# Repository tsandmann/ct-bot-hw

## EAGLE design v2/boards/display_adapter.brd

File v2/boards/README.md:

# ct-Bot v2 prototype boards

These boards (mainboard, teensy mcu board, and sensor boards) are ***prototypes*** just for ***development and testing***. They are provided "as is" without warranty of any kind.

## Known issues and notes

Please note: these problem lists may be highly incomplete, as not all functions have been tested yet!

### [Mainboard](../schematics/mainboard_0.9.2.pdf)

* Positioning of J2 is inappropriate
* TBC

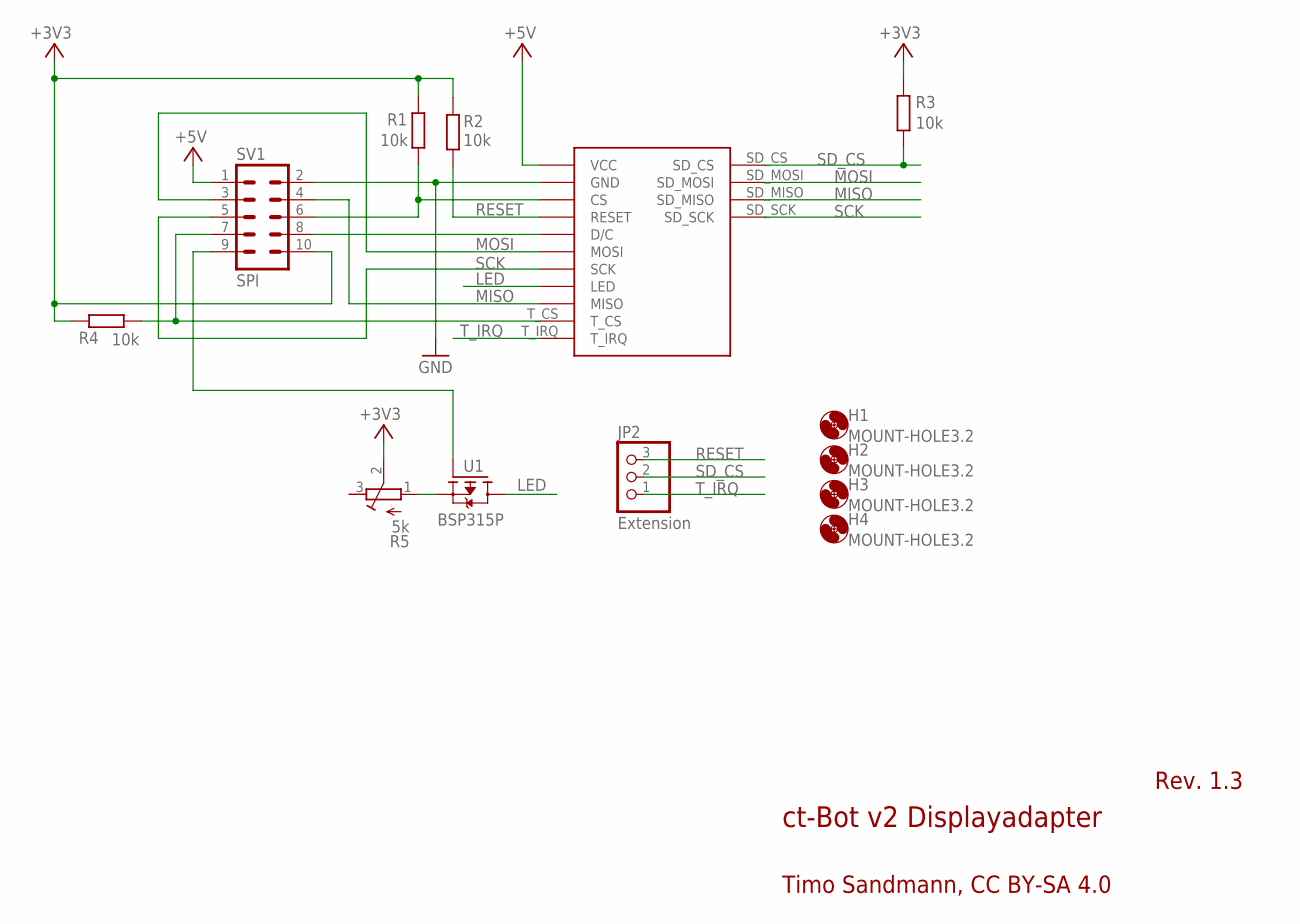
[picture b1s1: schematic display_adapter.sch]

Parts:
H1, H2, H3, H4: MOUNT-HOLE3.2; 3,2
J1: SPI_TFT_DISPLAY_TOUCH; SPI_DISPLAY_TOUCH
JP2: Extension; 1X03
R1, R2, R3, R4: 10k; 0204/7
R5: 5k; RTRIM64W
SV1: SPI; ML10
U1: BSP315P; PG-SOT-223

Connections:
+3V3: R1.2, R2.2, R3.2, R4.2, R5.2 (S), SV1.10
+5V: J1.VCC, SV1.1
GND: J1.GND, SV1.2
LED: J1.LED, U1.2 (D), U1.4 (D)
MISO: J1.MISO, J1.SD_MISO, J1.T_MISO (MISO), SV1.4
MOSI: J1.MOSI, J1.SD_MOSI, J1.T_MOSI (MOSI), SV1.3
unnamed: SV1.9, U1.1 (G)
unnamed: R5.1 (A), U1.3 (S)
unnamed: J1.CS, R1.1, SV1.6
unnamed: J1.D/C, SV1.8
unnamed: J1.T_CS, R4.1, SV1.7
RESET: J1.RESET, JP2.3, R2.1
SCK: J1.SCK, J1.SD_SCK, J1.T_SCK (SCK), SV1.5
SD_CS: J1.SD_CS, JP2.2, R3.1
T_IRQ: J1.T_IRQ, JP2.1

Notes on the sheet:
ct-Bot v2 Displayadapter
Rev. 1.3
Timo Sandmann, CC BY-SA 4.0

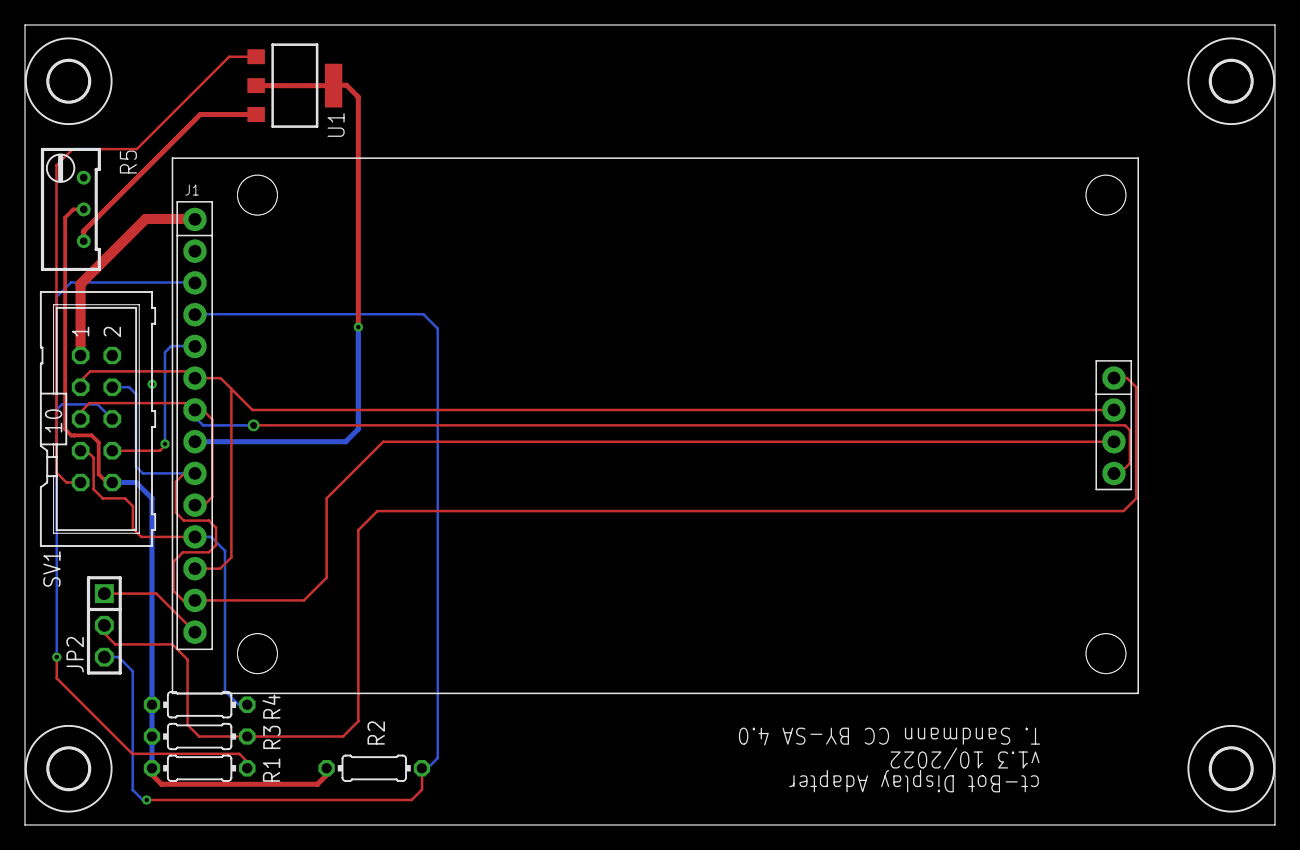
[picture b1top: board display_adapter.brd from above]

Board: 2 copper layers, 100.0 x 64.0 mm, 13 parts (0 on the bottom side), 15 nets.

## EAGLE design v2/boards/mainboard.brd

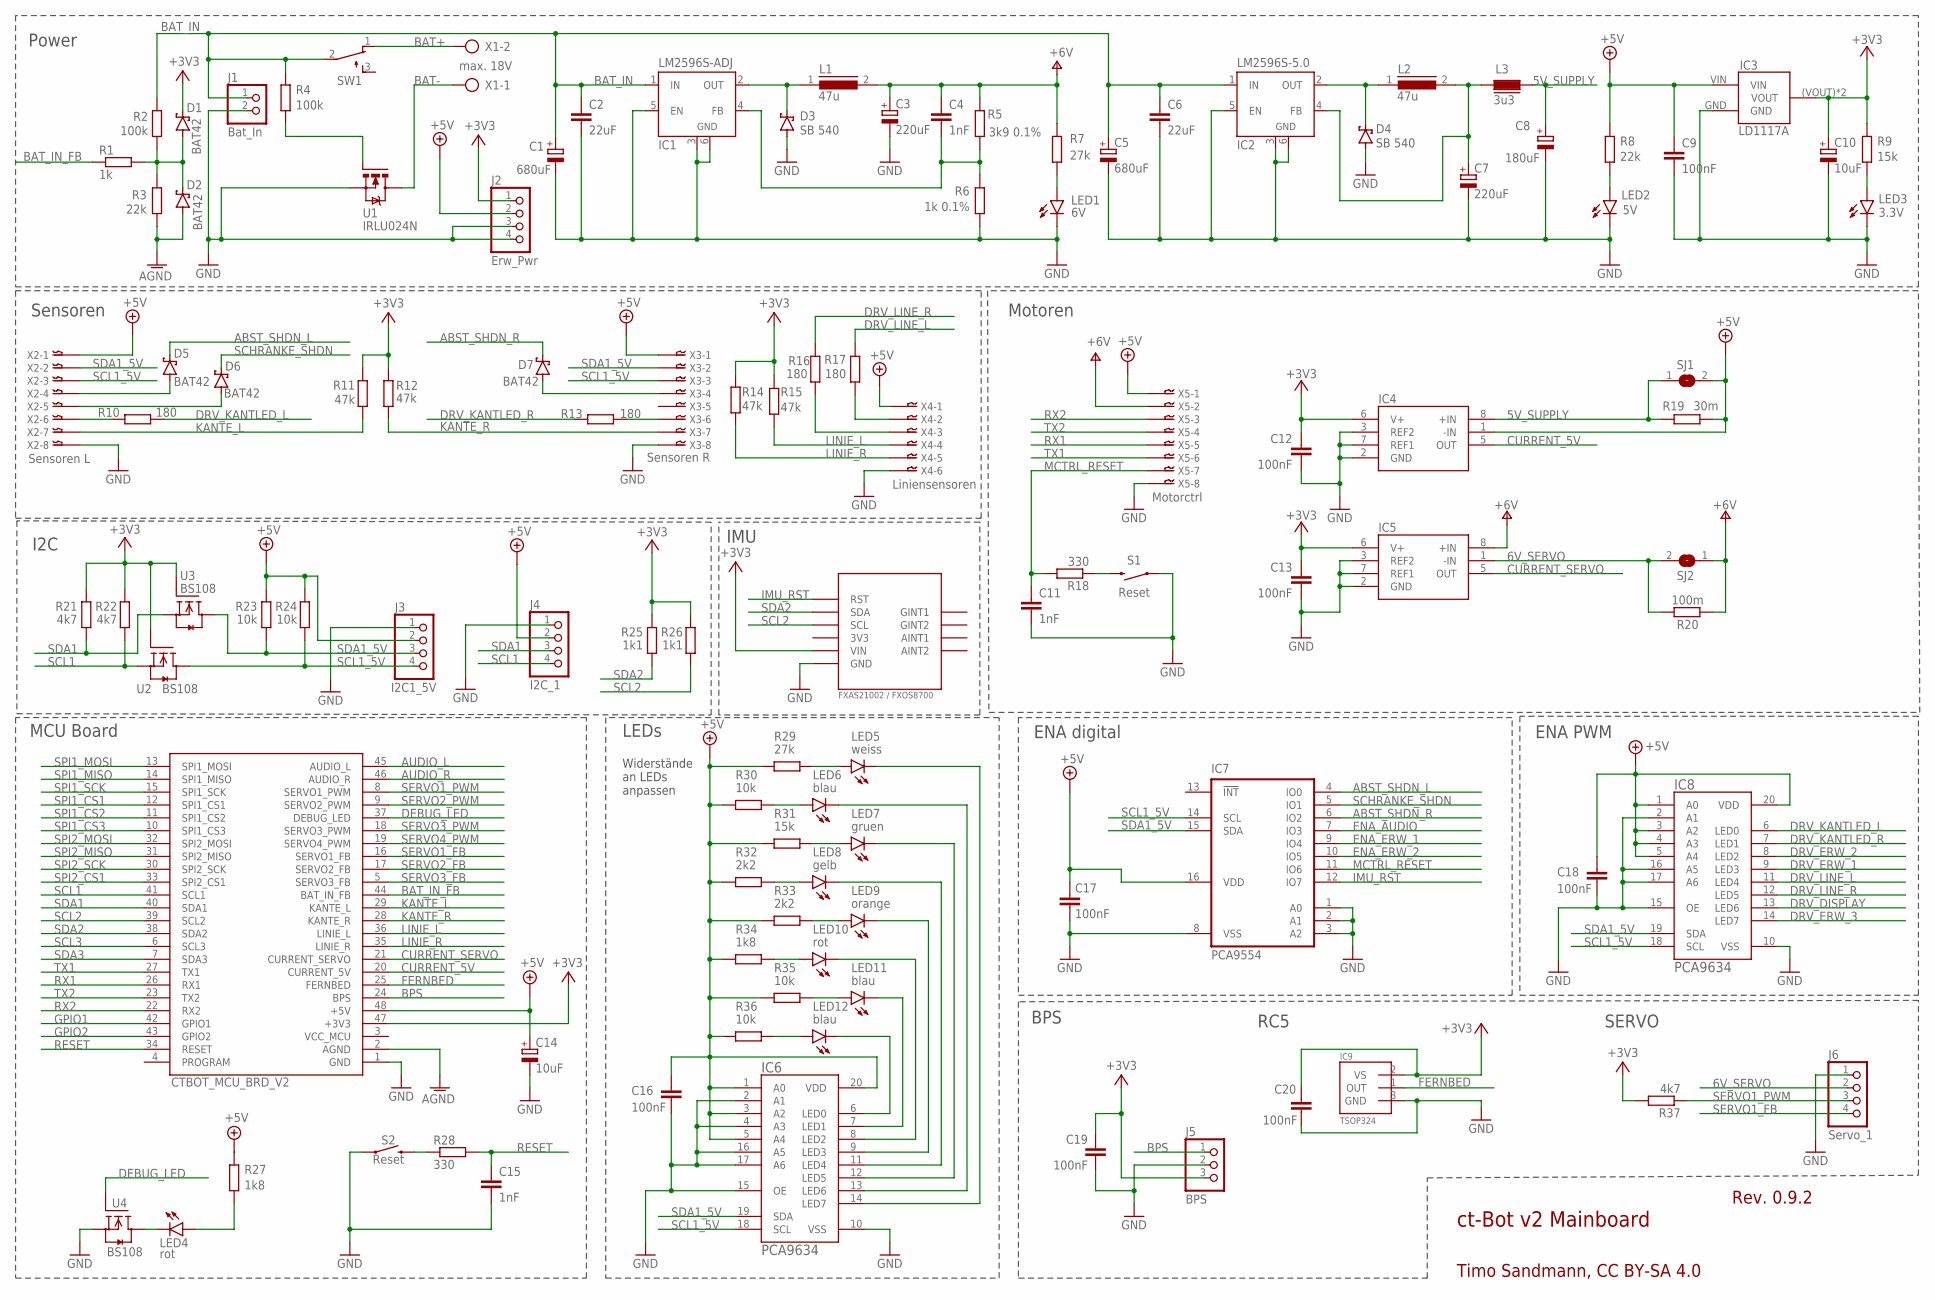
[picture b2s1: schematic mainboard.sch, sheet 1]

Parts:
C1, C5: 680uF; E5-10,5
C2, C6: 22uF; C025-025X050
C3, C7: 220uF; E5-10,5
C4, C11, C15: 1nF; C025-025X050
C8: 180uF; E3,5-8
C9, C16, C17, C18, C19, C20: 100nF; C025-025X050
C10: 10uF; E2-5
C12, C13: 100nF; C0805
C14: 10uF; TT2D5L
D1, D2: BAT42; DO35-7
D3, D4: SB 540; DO201T15
D5, D6, D7: BAT42; 0207/2V
IC1: LM2596S-ADJ; TO263-5
IC2: LM2596S-5.0; TO263-5
IC3: LD1117A; LD1117SOT-223
IC4, IC5: INA28AID; SO08
IC6, IC8: PCA9634; SO20W
IC7: PCA9554; SO16W
IC9: TSOP324
J1: Bat_In; 1X02
J2: Erw_Pwr; 1X04
J3: I2C1_5V; 1X04
J4: I2C_1; 1X04
J5: BPS; 1X03
J6: Servo_1; 1X04
L1, L2: 47u; 09HCP
L3: 3u3; FASTRON_07HCP_INDUCTOR
LED1: 6V; LED3MM
LED2: 5V; LED3MM
LED3: 3.3V; LED3MM
LED4, LED10: rot; LED3MM
LED5: weiss; LED3MM
LED6, LED11, LED12: blau; LED3MM
LED7: gruen; LED3MM
LED8: gelb; LED3MM
LED9: orange; LED3MM
MCU: CTBOT_MCU_BRD_V2; DIP48
R1: 1k; 0204/7
R2: 100k; 0204/7
R3: 22k; 0204/7
R4: 100k; 0204V
R5: 3k9 0.1%; 0204V
R6: 1k 0.1%; 0204V
R7, R29: 27k; 0204V
R8: 22k; 0204V
R9, R31: 15k; 0204V
R10, R13, R16, R17: 180; 0204V
R11, R12: 47k; 0204V
R14, R15: 47k; 0204/7
R18, R28: 330; 0204V
R19: 30m; R2512
R20: 100m; R2512
R21, R22, R37: 4k7; 0204/7
R23, R24, R30, R35, R36: 10k; 0204V
R25, R26: 1k1; 0204/7
R27, R34: 1k8; 0204V
R32, R33: 2k2; 0204V
S1, S2: Reset; TACTILE_SWITCH_PTH_6.0MM
SJ1, SJ2: SJ
SW1: TL32PO; TL3XPO
U1: IRLU024N; TO251AA
U2, U3, U4: BS108; SOT54E
U$10: IMU; NXP_9DOF
X1: max. 18V; AK500/2-H
X2: Sensoren L; B8B-XH
X3: Sensoren R; B8B-XH
X4: Liniensensoren; B6B-XH
X5: Motorctrl; B8B-XH

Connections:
5V_SUPPLY: C8.+, IC4.8 (+IN), L3.2, R19.1, SJ1.1
6V_SERVO: IC5.1 (-IN), J6.2, R20.2, SJ2.2; also elsewhere on the board
+3V3: C10.+, C12.1, C13.1, C19.1, C20.1, D1.C, IC3.(VOUT) (VOUT), IC3.VOUT, IC4.6 (V+), IC5.6 (V+), IC9.2 (VS), J2.1, J5.3, MCU.47 (+3V3), R9.2, R11.2, R12.1, R14.2, R15.2, R21.2, R22.2, R25.2, R26.2, R37.2, U2.G, U3.G, U$10.VIN; also elsewhere on the board
+5V: C9.1, C14.+, C16.1, C17.1, C18.1, IC3.VIN, IC4.1 (-IN), IC6.1 (A0), IC6.3 (A2), IC6.5 (A4), IC6.20 (VDD), IC7.16 (VDD), IC8.1 (A0), IC8.3 (A2), IC8.4 (A3), IC8.5 (A4), IC8.20 (VDD), J2.2, J3.2, J4.2, MCU.48 (+5V), R8.2, R19.2, R23.2, R24.2, R27.2, R29.1, R30.1, R31.1, R32.1, R33.1, R34.1, R35.1, R36.1, SJ1.2, X2.P$1, X3.P$1, X4.P$1, X5.P$1; also elsewhere on the board
+6V: C3.+, C4.1, IC5.8 (+IN), L1.2, R5.2, R7.1, R20.1, SJ2.1, X5.P$2
ABST_SHDN_L: D5.2 (C), IC7.4 (IO0)
ABST_SHDN_R: D7.2 (C), IC7.6 (IO2)
AGND: D2.A, MCU.2 (AGND), R3.1; also elsewhere on the board
AUDIO_L: MCU.45 (AUDIO_L); also elsewhere on the board
AUDIO_R: MCU.46 (AUDIO_R); also elsewhere on the board
BAT+: SW1.1 (O), X1.2
BAT-: U1.2 (D), U1.4 (D), X1.1
BAT_IN: C1.+, C2.1, C5.+, C6.1, IC1.1 (IN), IC2.1 (IN), J1.1, R2.2, R4.2, SW1.2; also elsewhere on the board
BAT_IN_FB: MCU.44 (BAT_IN_FB), R1.1
BPS: J5.1, MCU.24 (BPS)
CURRENT_5V: IC4.5 (OUT), MCU.20 (CURRENT_5V)
CURRENT_SERVO: IC5.5 (OUT), MCU.21 (CURRENT_SERVO)
DEBUG_LED: MCU.37 (DEBUG_LED), U4.G
DRV_DISPLAY: IC8.13 (LED6); also elsewhere on the board
DRV_ERW_1: IC8.9 (LED3); also elsewhere on the board
DRV_ERW_2: IC8.8 (LED2); also elsewhere on the board
DRV_ERW_3: IC8.14 (LED7); also elsewhere on the board
DRV_KANTLED_L: IC8.6 (LED0), R10.2
DRV_KANTLED_R: IC8.7 (LED1), R13.1
DRV_LINE_L: IC8.11 (LED4), R17.2
DRV_LINE_R: IC8.12 (LED5), R16.2
ENA_AUDIO: IC7.7 (IO3); also elsewhere on the board
ENA_ERW_1: IC7.9 (IO4); also elsewhere on the board
ENA_ERW_2: IC7.10 (IO5); also elsewhere on the board
FERNBED: IC9.1 (OUT), MCU.25 (FERNBED)
GND: C1.-, C2.2, C3.-, C5.-, C6.2, C7.-, C8.-, C9.2, C10.-, C11.2, C12.2, C13.2, C14.-, C15.2, C16.2, C17.2, C18.2, C19.2, C20.2, D3.A, D4.A, IC1.3 (GND), IC1.5 (EN), IC1.6 (GND), IC2.3 (GND), IC2.5 (EN), IC2.6 (GND), IC3.GND, IC4.2 (GND), IC4.3 (REF2), IC4.7 (REF1), IC5.2 (GND), IC5.3 (REF2), IC5.7 (REF1), IC6.2 (A1), IC6.4 (A3), IC6.10 (VSS), IC6.15 (OE), IC6.16 (A5), IC6.17 (A6), IC7.1 (A0), IC7.2 (A1), IC7.3 (A2), IC7.8 (VSS), IC8.2 (A1), IC8.10 (VSS), IC8.15 (OE), IC8.16 (A5), IC8.17 (A6), IC9.3 (GND), J1.2, J2.3, J2.4, J3.1, J4.1, J5.2, J6.1, LED1.K (C), LED2.K (C), LED3.K (C), MCU.1 (GND), R6.1, S1.1, S2.1, U1.3 (S), U4.S, U$10.GND, X2.P$8, X3.P$8, X4.P$6, X5.P$8; also elsewhere on the board
GPIO1: MCU.42 (GPIO1); also elsewhere on the board
GPIO2: MCU.43 (GPIO2); also elsewhere on the board
IMU_RST: IC7.12 (IO7), U$10.RST; also elsewhere on the board
KANTE_L: MCU.29 (KANTE_L), R11.1, X2.P$7
KANTE_R: MCU.28 (KANTE_R), R12.2, X3.P$7
LINIE_L: MCU.36 (LINIE_L), R15.1, X4.P$4
LINIE_R: MCU.35 (LINIE_R), R14.1, X4.P$5
MCTRL_RESET: C11.1, IC7.11 (IO6), R18.2, X5.P$7
unnamed: R16.1, X4.P$3
unnamed: LED3.A, R9.1
unnamed: D1.A, D2.C, R1.2, R2.1, R3.2
unnamed: R18.1, S1.3 (2)
unnamed: IC6.6 (LED0), LED12.K (C)
unnamed: IC6.7 (LED1), LED11.K (C)
unnamed: LED1.A, R7.2
unnamed: C4.2, IC1.4 (FB), R5.1, R6.2
unnamed: LED2.A, R8.1
unnamed: IC6.8 (LED2), LED10.K (C)
unnamed: R28.1, S2.3 (2)
unnamed: IC6.9 (LED3), LED9.K (C)
unnamed: IC6.11 (LED4), LED8.K (C)
unnamed: IC6.12 (LED5), LED7.K (C)
unnamed: IC6.13 (LED6), LED6.K (C)
unnamed: IC6.14 (LED7), LED5.K (C)
unnamed: LED5.A, R29.2
unnamed: LED6.A, R30.2
unnamed: LED7.A, R31.2
unnamed: LED8.A, R32.2
unnamed: LED9.A, R33.2
unnamed: LED10.A, R34.2
unnamed: LED11.A, R35.2
unnamed: LED12.A, R36.2
unnamed: LED4.A, R27.1
unnamed: LED4.K (C), U4.D
unnamed: R17.1, X4.P$2
unnamed: R4.1, U1.1 (G)
unnamed: R10.1, X2.P$6
unnamed: R13.2, X3.P$6
RESET: C15.1, MCU.34 (RESET), R28.2
RX1: MCU.26 (RX1), X5.P$5; also elsewhere on the board
RX2: MCU.22 (RX2), X5.P$3
SCHRANKE_SHDN: D6.2 (C), IC7.5 (IO1)
SCL1: J4.4, MCU.41 (SCL1), R22.1, U2.S
SCL1_5V: IC6.18 (SCL), IC7.14 (SCL), IC8.18 (SCL), J3.4, R24.1, U2.D, X2.P$3, X3.P$3
SCL2: MCU.39 (SCL2), R26.1, U$10.SCL; also elsewhere on the board
SCL3: MCU.6 (SCL3); also elsewhere on the board
SDA1: J4.3, MCU.40 (SDA1), R21.1, U3.S
SDA1_5V: IC6.19 (SDA), IC7.15 (SDA), IC8.19 (SDA), J3.3, R23.1, U3.D, X2.P$2, X3.P$2
SDA2: MCU.38 (SDA2), R25.1, U$10.SDA; also elsewhere on the board
SDA3: MCU.7 (SDA3); also elsewhere on the board
SERVO1_FB: J6.4, MCU.16 (SERVO1_FB)
SERVO1_PWM: J6.3, MCU.8 (SERVO1_PWM), R37.1
SERVO2_FB: MCU.17 (SERVO2_FB); also elsewhere on the board
SERVO2_PWM: MCU.9 (SERVO2_PWM); also elsewhere on the board
SERVO3_FB: MCU.5 (SERVO3_FB); also elsewhere on the board
SERVO3_PWM: MCU.18 (SERVO3_PWM); also elsewhere on the board
SERVO4_PWM: MCU.19 (SERVO4_PWM); also elsewhere on the board
SPI1_CS1: MCU.12 (SPI1_CS1); also elsewhere on the board
SPI1_CS2: MCU.11 (SPI1_CS2); also elsewhere on the board
SPI1_CS3: MCU.10 (SPI1_CS3); also elsewhere on the board
SPI1_MISO: MCU.14 (SPI1_MISO); also elsewhere on the board
SPI1_MOSI: MCU.13 (SPI1_MOSI); also elsewhere on the board
SPI1_SCK: MCU.15 (SPI1_SCK); also elsewhere on the board
SPI2_CS1: MCU.33 (SPI2_CS1); also elsewhere on the board
SPI2_MISO: MCU.31 (SPI2_MISO); also elsewhere on the board
SPI2_MOSI: MCU.32 (SPI2_MOSI); also elsewhere on the board
SPI2_SCK: MCU.30 (SPI2_SCK); also elsewhere on the board
TX1: MCU.27 (TX1), X5.P$6; also elsewhere on the board
TX2: MCU.23 (TX2), X5.P$4
V5_L2: D4.C, IC2.2 (OUT), L2.1
V5_L3: C7.+, IC2.4 (FB), L2.2, L3.1
V6_L1: D3.C, IC1.2 (OUT), L1.1
VCC_MCU: MCU.3 (VCC_MCU)
VL53L0X_SHUT_L: D5.1 (A), X2.P$4
VL53L0X_SHUT_R: D7.1 (A), X3.P$4
VL6180X_SHDN: D6.1 (A), X2.P$5

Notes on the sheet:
ct-Bot v2 Mainboard
Rev. 0.9.2
Timo Sandmann, CC BY-SA 4.0
Widerstände an LEDs anpassen
Power
Sensoren
I2C
MCU Board
ENA digital
ENA PWM
LEDs
RC5
Motoren
BPS
SERVO
IMU

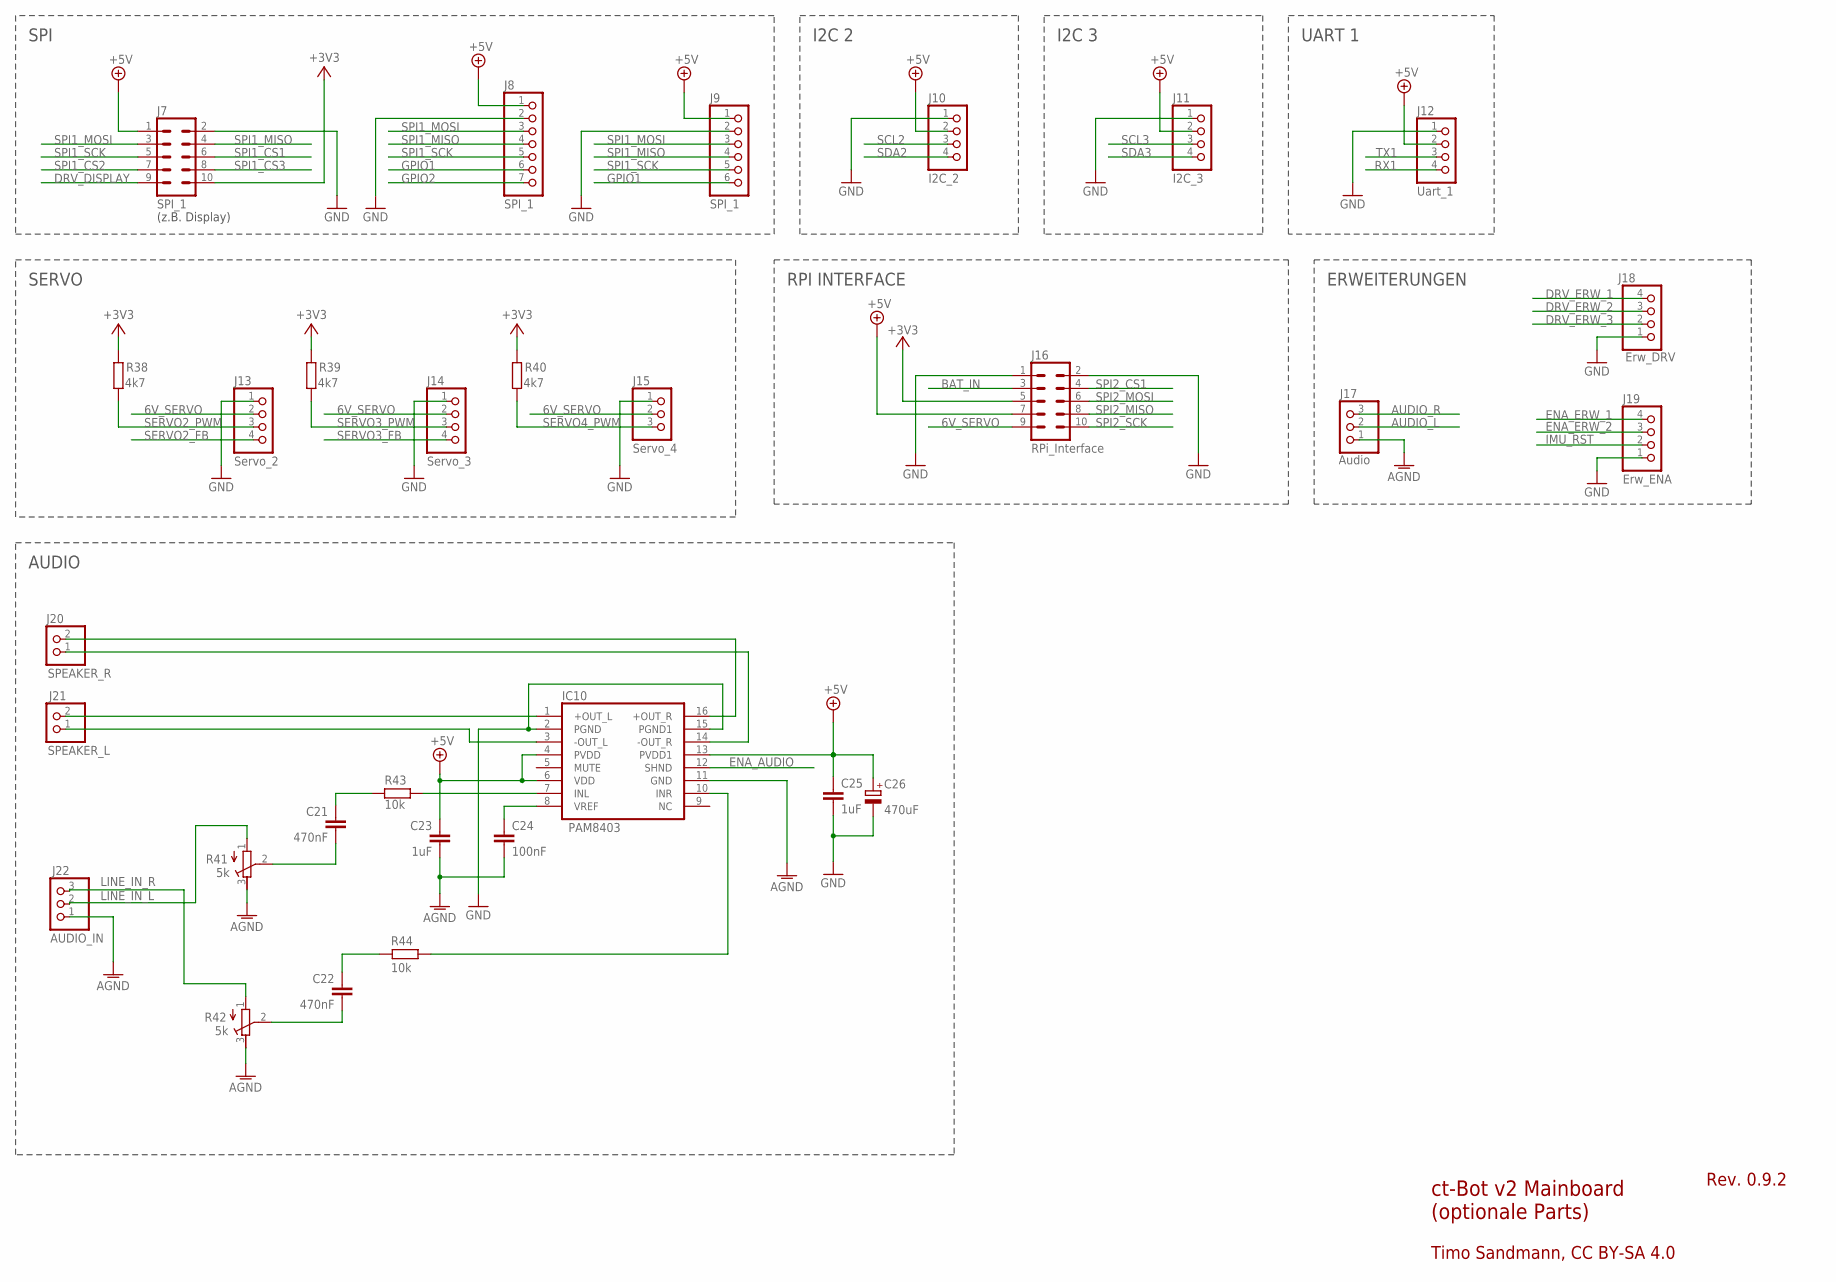
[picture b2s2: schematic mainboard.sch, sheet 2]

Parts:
C21, C22: 470nF; C025-025X050
C23, C25: 1uF; C025-025X050
C24: 100nF; C025-025X050
C26: 470uF; E3,5-8
IC10: PAM8403; SOP-16
J7: SPI_1; ML10
J8: SPI_1; 1X07
J9: SPI_1; 1X06
J10: I2C_2; 1X04
J11: I2C_3; 1X04
J12: Uart_1; 1X04
J13: Servo_2; 1X04
J14: Servo_3; 1X04
J15: Servo_4; 1X03
J16: RPi_Interface; ML10
J17: Audio; 1X03
J18: Erw_DRV; 1X04
J19: Erw_ENA; 1X04
J20: SPEAKER_R; 1X02
J21: SPEAKER_L; 1X02
J22: AUDIO_IN; 1X03
R38, R39, R40: 4k7; 0204/7
R41, R42: 5k; RTRIM64W
R43, R44: 10k; 0204V

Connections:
6V_SERVO: J13.2, J14.2, J15.2, J16.9; also elsewhere on the board
+3V3: J7.10, J16.5, R38.2, R39.2, R40.2; also elsewhere on the board
+5V: C23.1, C25.1, C26.+, IC10.4 (PVDD), IC10.6 (VDD), IC10.13 (PVDD1), J7.1, J8.1, J9.1, J10.2, J11.2, J12.2, J16.7; also elsewhere on the board
AGND: C23.2, C24.2, IC10.11 (GND), J17.1, J22.1, R41.3 (E), R42.3 (E); also elsewhere on the board
AUDIO_L: J17.2; also elsewhere on the board
AUDIO_R: J17.3; also elsewhere on the board
BAT_IN: J16.3; also elsewhere on the board
DRV_DISPLAY: J7.9; also elsewhere on the board
DRV_ERW_1: J18.4; also elsewhere on the board
DRV_ERW_2: J18.3; also elsewhere on the board
DRV_ERW_3: J18.2; also elsewhere on the board
ENA_AUDIO: IC10.12 (SHND); also elsewhere on the board
ENA_ERW_1: J19.4; also elsewhere on the board
ENA_ERW_2: J19.3; also elsewhere on the board
GND: C25.2, C26.-, IC10.2 (PGND), IC10.15 (PGND1), J7.2, J8.2, J9.2, J10.1, J11.1, J12.1, J13.1, J14.1, J15.1, J16.1, J16.2, J18.1, J19.1; also elsewhere on the board
GPIO1: J8.6, J9.6; also elsewhere on the board
GPIO2: J8.7; also elsewhere on the board
IMU_RST: J19.2; also elsewhere on the board
LINE_IN_L: J22.2, R41.1 (A)
LINE_IN_R: J22.3, R42.1 (A)
unnamed: IC10.1 (+OUT_L), J21.2
unnamed: IC10.3 (-OUT_L), J21.1
unnamed: C24.1, IC10.8 (VREF)
unnamed: C22.2, R42.2 (S)
unnamed: IC10.7 (INL), R43.1
unnamed: C21.1, R43.2
unnamed: C21.2, R41.2 (S)
unnamed: IC10.14 (-OUT_R), J20.1
unnamed: IC10.16 (+OUT_R), J20.2
unnamed: IC10.10 (INR), R44.1
unnamed: C22.1, R44.2
RX1: J12.4; also elsewhere on the board
SCL2: J10.3; also elsewhere on the board
SCL3: J11.3; also elsewhere on the board
SDA2: J10.4; also elsewhere on the board
SDA3: J11.4; also elsewhere on the board
SERVO2_FB: J13.4; also elsewhere on the board
SERVO2_PWM: J13.3, R38.1; also elsewhere on the board
SERVO3_FB: J14.4; also elsewhere on the board
SERVO3_PWM: J14.3, R39.1; also elsewhere on the board
SERVO4_PWM: J15.3, R40.1; also elsewhere on the board
SPI1_CS1: J7.6; also elsewhere on the board
SPI1_CS2: J7.7; also elsewhere on the board
SPI1_CS3: J7.8; also elsewhere on the board
SPI1_MISO: J7.4, J8.4, J9.4; also elsewhere on the board
SPI1_MOSI: J7.3, J8.3, J9.3; also elsewhere on the board
SPI1_SCK: J7.5, J8.5, J9.5; also elsewhere on the board
SPI2_CS1: J16.4; also elsewhere on the board
SPI2_MISO: J16.8; also elsewhere on the board
SPI2_MOSI: J16.6; also elsewhere on the board
SPI2_SCK: J16.10; also elsewhere on the board
TX1: J12.3; also elsewhere on the board

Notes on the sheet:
(z.B. Display)
ct-Bot v2 Mainboard (optionale Parts)
Rev. 0.9.2
SPI
I2C 2
UART 1
SERVO
ERWEITERUNGEN
AUDIO
RPI INTERFACE
I2C 3
Timo Sandmann, CC BY-SA 4.0

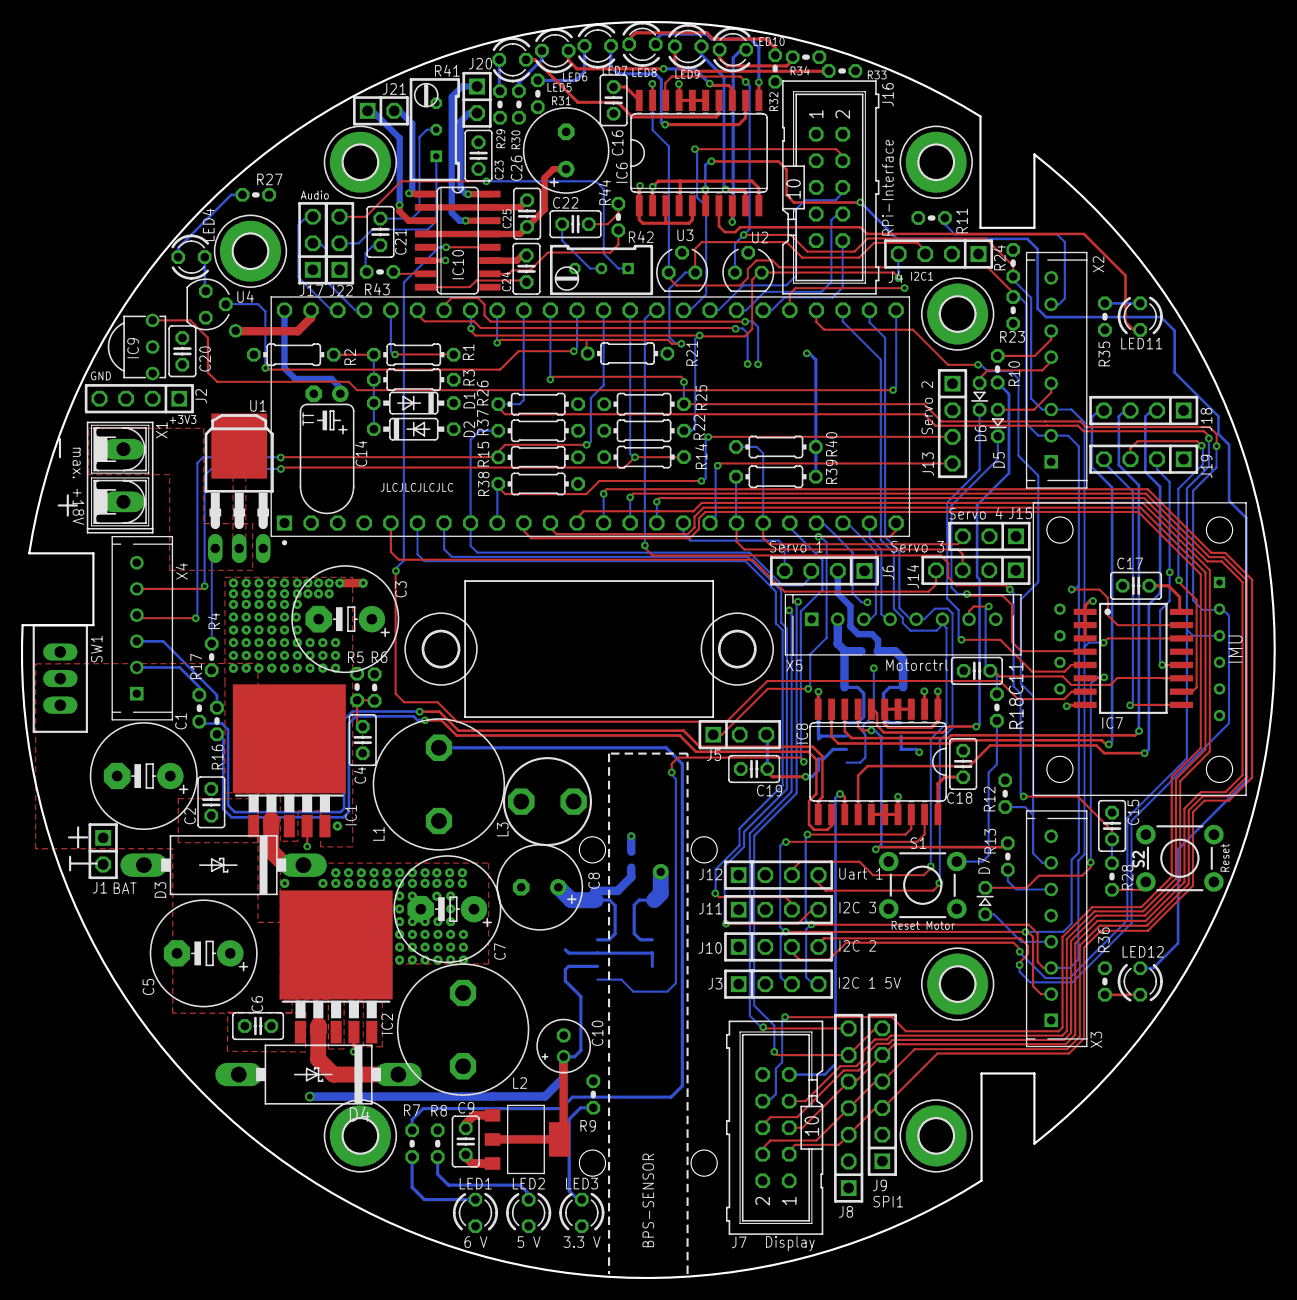
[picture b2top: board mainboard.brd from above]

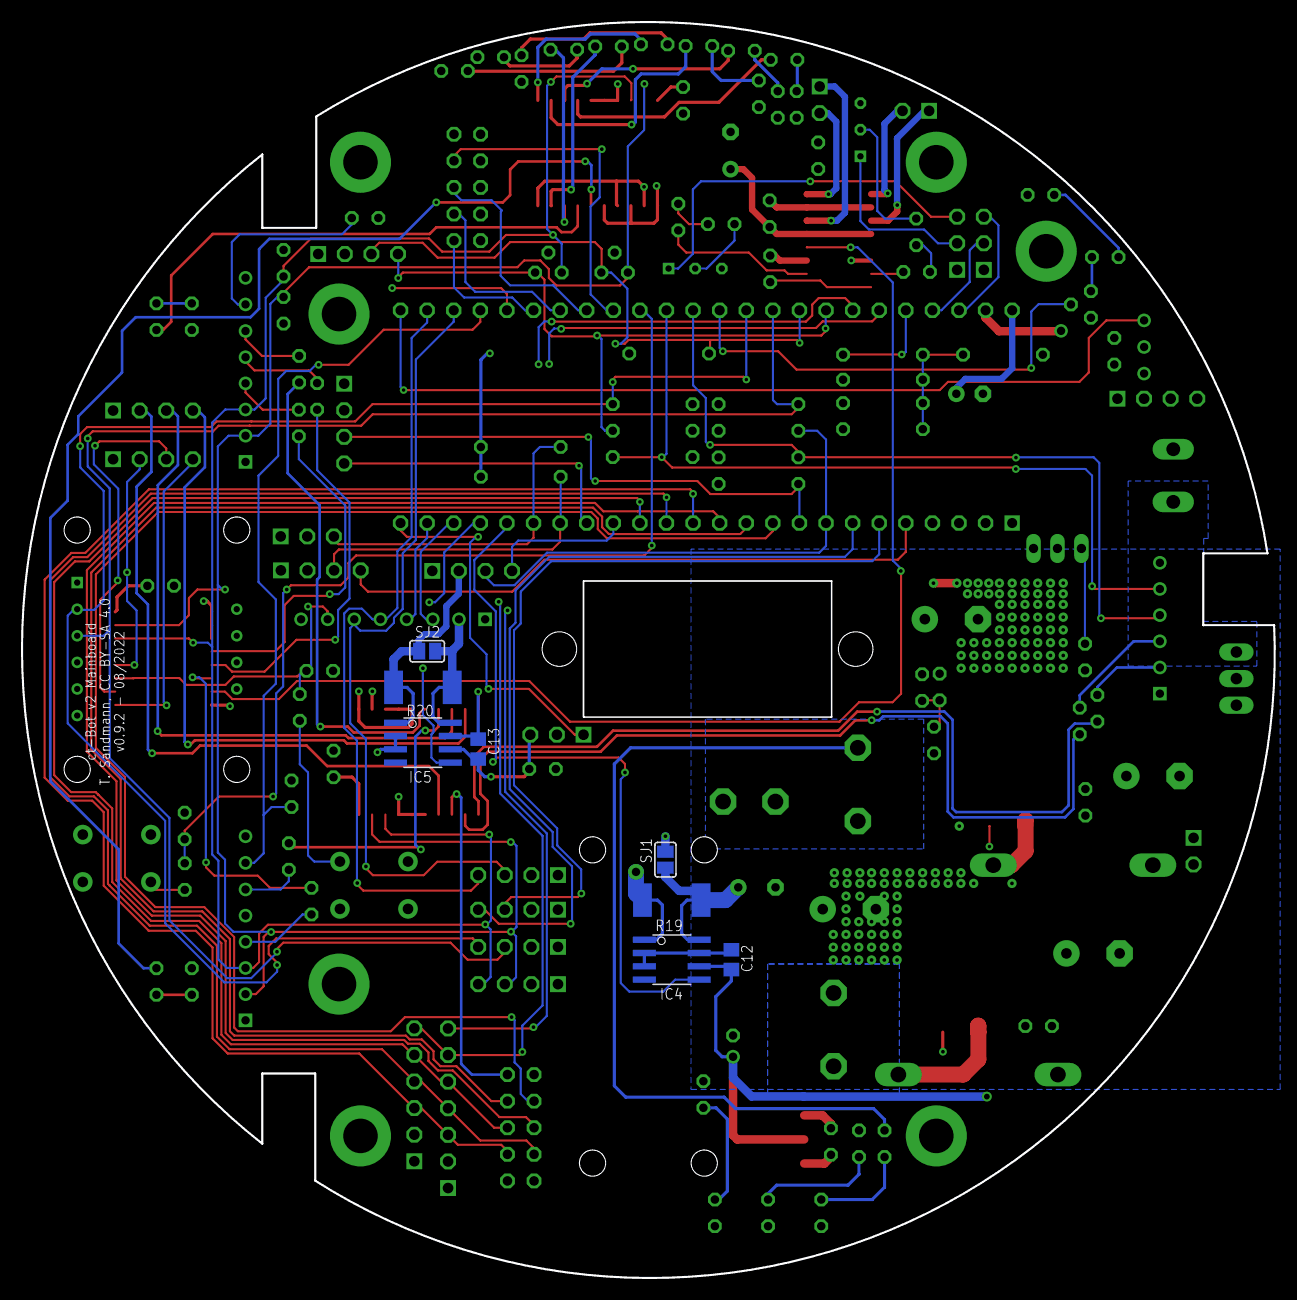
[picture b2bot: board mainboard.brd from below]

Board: 4 copper layers, 119.7 x 120.0 mm, 149 parts (8 on the bottom side), 119 nets.

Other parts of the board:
U$1, U$2, U$3, U$4, U$5, U$6, U$7: 3,3-PAD
U$8, U$9: 3,3

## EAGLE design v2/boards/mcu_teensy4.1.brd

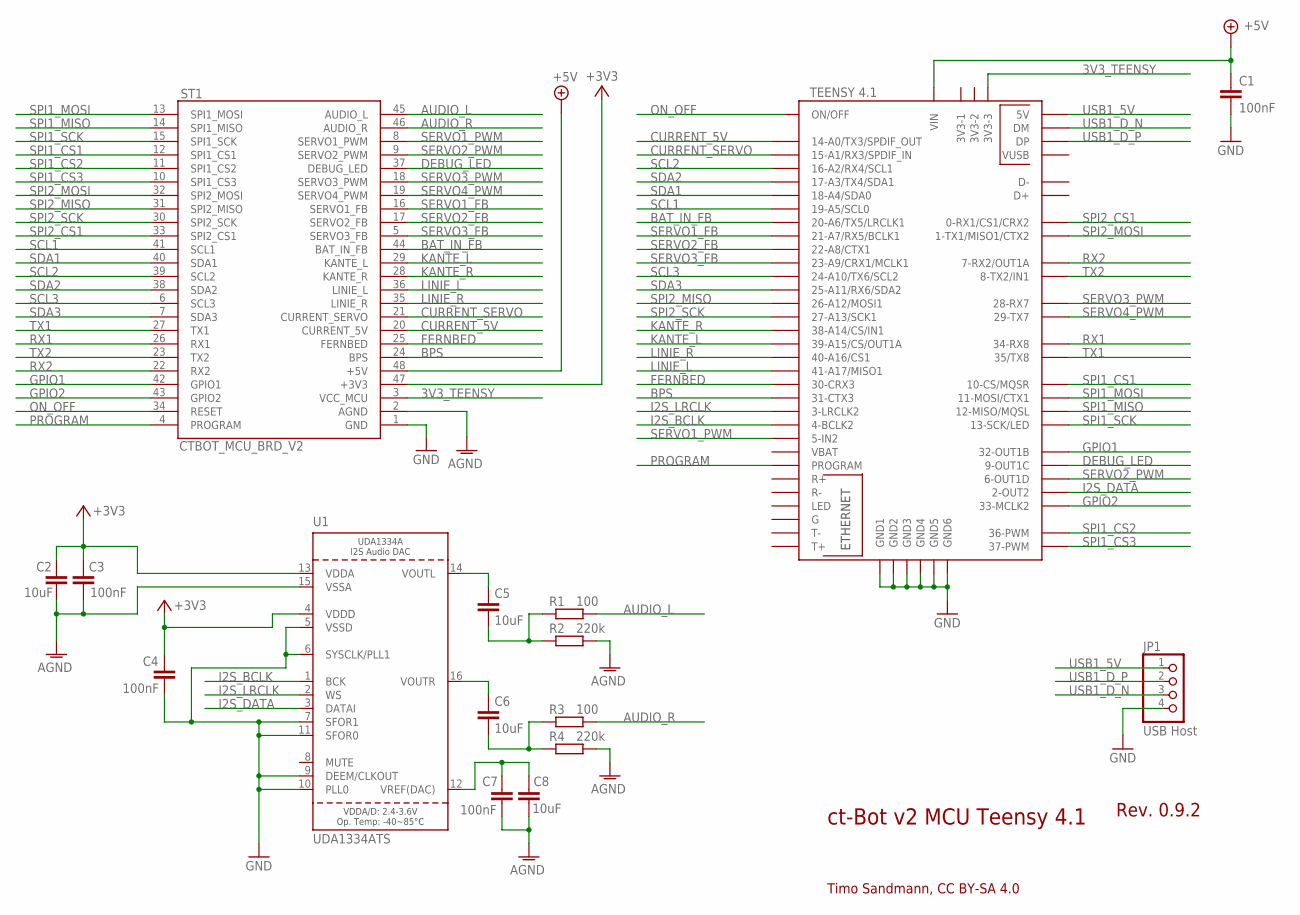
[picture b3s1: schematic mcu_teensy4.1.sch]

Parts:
C1, C3, C4, C7: 100nF; C0805
C2, C5, C6, C8: 10uF; C0805
JP1: USB Host; 1X04/90
R1, R3: 100; R0805
R2, R4: 220k; R0805
ST1: CTBOT_MCU_BRD_V2; DIP48
U1: UDA1334ATS; SSOP16_4.4MM
U$1: TEENSY41

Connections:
3V3_TEENSY: ST1.3 (VCC_MCU), U$1.3V3-3
+3V3: C2.1, C3.2, C4.2, ST1.47 (+3V3), U1.4 (VDDD), U1.13 (VDDA)
+5V: C1.1, ST1.48 (+5V), U$1.VIN
AGND: C2.2, C3.1, C7.1, C8.1, R2.2, R4.2, ST1.2 (AGND), U1.15 (VSSA)
AUDIO_L: R1.2, ST1.45 (AUDIO_L)
AUDIO_R: R3.2, ST1.46 (AUDIO_R)
BAT_IN_FB: ST1.44 (BAT_IN_FB), U$1.20-A6/TX5/LRCLK1
BPS: ST1.24 (BPS), U$1.31-CTX3
CURRENT_5V: ST1.20 (CURRENT_5V), U$1.14-A0/TX3/SPDIF_OUT
CURRENT_SERVO: ST1.21 (CURRENT_SERVO), U$1.15-A1/RX3/SPDIF_IN
DEBUG_LED: ST1.37 (DEBUG_LED), U$1.9-OUT1C
FERNBED: ST1.25 (FERNBED), U$1.30-CRX3
GND: C1.2, C4.1, JP1.4, ST1.1 (GND), U1.5 (VSSD), U1.6 (SYSCLK/PLL1), U1.7 (SFOR1), U1.9 (DEEM/CLKOUT), U1.10 (PLL0), U1.11 (SFOR0), U$1.GND1, U$1.GND2, U$1.GND3, U$1.GND4, U$1.GND5, U$1.GND6
GPIO1: ST1.42 (GPIO1), U$1.32-OUT1B
GPIO2: ST1.43 (GPIO2), U$1.33-MCLK2
I2S_BCLK: U1.1 (BCK), U$1.4-BCLK2
I2S_DATA: U1.3 (DATAI), U$1.2-OUT2
I2S_LRCLK: U1.2 (WS), U$1.3-LRCLK2
KANTE_L: ST1.29 (KANTE_L), U$1.39-A15/CS/OUT1A
KANTE_R: ST1.28 (KANTE_R), U$1.38-A14/CS/IN1
LINIE_L: ST1.36 (LINIE_L), U$1.41-A17/MISO1
LINIE_R: ST1.35 (LINIE_R), U$1.40-A16/CS1
unnamed: C7.2, C8.2, U1.12 (VREF(DAC))
unnamed: C5.1, U1.14 (VOUTL)
unnamed: C6.1, U1.16 (VOUTR)
unnamed: C5.2, R1.1, R2.1
unnamed: C6.2, R3.1, R4.1
ON_OFF: ST1.34 (RESET), U$1.ON/OFF
PROGRAM: ST1.4 (PROGRAM), U$1.PROGRAM
RX1: ST1.26 (RX1), U$1.34-RX8
RX2: ST1.22 (RX2), U$1.7-RX2/OUT1A
SCL1: ST1.41 (SCL1), U$1.19-A5/SCL0
SCL2: ST1.39 (SCL2), U$1.16-A2/RX4/SCL1
SCL3: ST1.6 (SCL3), U$1.24-A10/TX6/SCL2
SDA1: ST1.40 (SDA1), U$1.18-A4/SDA0
SDA2: ST1.38 (SDA2), U$1.17-A3/TX4/SDA1
SDA3: ST1.7 (SDA3), U$1.25-A11/RX6/SDA2
SERVO1_FB: ST1.16 (SERVO1_FB), U$1.21-A7/RX5/BCLK1
SERVO1_PWM: ST1.8 (SERVO1_PWM), U$1.5-IN2
SERVO2_FB: ST1.17 (SERVO2_FB), U$1.22-A8/CTX1
SERVO2_PWM: ST1.9 (SERVO2_PWM), U$1.6-OUT1D
SERVO3_FB: ST1.5 (SERVO3_FB), U$1.23-A9/CRX1/MCLK1
SERVO3_PWM: ST1.18 (SERVO3_PWM), U$1.28-RX7
SERVO4_PWM: ST1.19 (SERVO4_PWM), U$1.29-TX7
SPI1_CS1: ST1.12 (SPI1_CS1), U$1.10-CS\MQSR (10-CS/MQSR)
SPI1_CS2: ST1.11 (SPI1_CS2), U$1.36-PWM
SPI1_CS3: ST1.10 (SPI1_CS3), U$1.37-PWM
SPI1_MISO: ST1.14 (SPI1_MISO), U$1.12-MISO/MQSL
SPI1_MOSI: ST1.13 (SPI1_MOSI), U$1.11-MOSI/CTX1
SPI1_SCK: ST1.15 (SPI1_SCK), U$1.13-SCK/LED
SPI2_CS1: ST1.33 (SPI2_CS1), U$1.0-RX1/CS1/CRX2
SPI2_MISO: ST1.31 (SPI2_MISO), U$1.26-A12/MOSI1
SPI2_MOSI: ST1.32 (SPI2_MOSI), U$1.1-TX1/MISO1/CTX2
SPI2_SCK: ST1.30 (SPI2_SCK), U$1.27-A13/SCK1
TX1: ST1.27 (TX1), U$1.35-TX8 (35/TX8)
TX2: ST1.23 (TX2), U$1.8-TX2/IN1
USB1_5V: JP1.1, U$1.+5V (5V)
USB1_D_N: JP1.3, U$1.DM
USB1_D_P: JP1.2, U$1.DP

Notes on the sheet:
ct-Bot v2 MCU Teensy 4.1
Rev. 0.9.2
Timo Sandmann, CC BY-SA 4.0

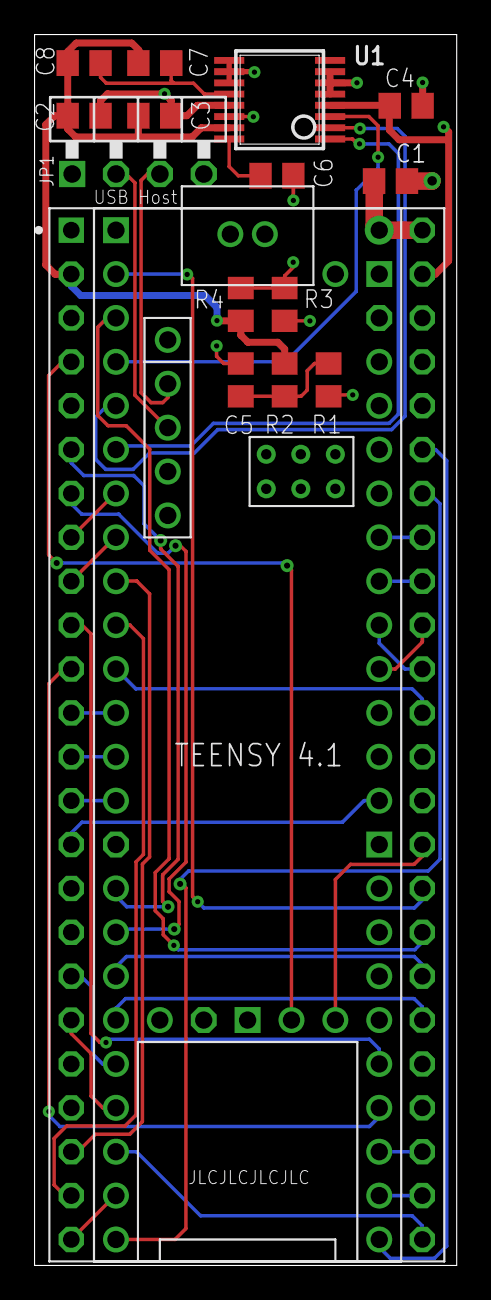
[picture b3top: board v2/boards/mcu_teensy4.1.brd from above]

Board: 4 copper layers, 24.4 x 71.2 mm, 16 parts (0 on the bottom side), 59 nets.

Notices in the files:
v2/boards/display_adapter.brd:
T. Sandmann CC BY-SA 4.0
v2/boards/mainboard.sch:
c't-Bot Hauptplatine v2; CC BY-SA 4.0, Timo Sandmann
v2/boards/mcu_teensy4.1.brd:
08/2022 T. Sandmann CC BY-SA 4.0
v2/boards/mcu_teensy4.1.sch:
c't-Bot v2 MCU Board; CC BY-SA 4.0, Timo Sandmann
v2/boards/prototype_pcbs/mcu_teensy4.1.brd:
05/2020 T. Sandmann CC BY-SA 4.0
parts and their libraries:
SparkFun-Switches: Licensing: Creative Commons ShareAlike 4.0 International - https://creativecommons.org/licenses/by-sa/4.0
